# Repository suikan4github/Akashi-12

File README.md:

# Akashi-12
Study PCB for RP2040

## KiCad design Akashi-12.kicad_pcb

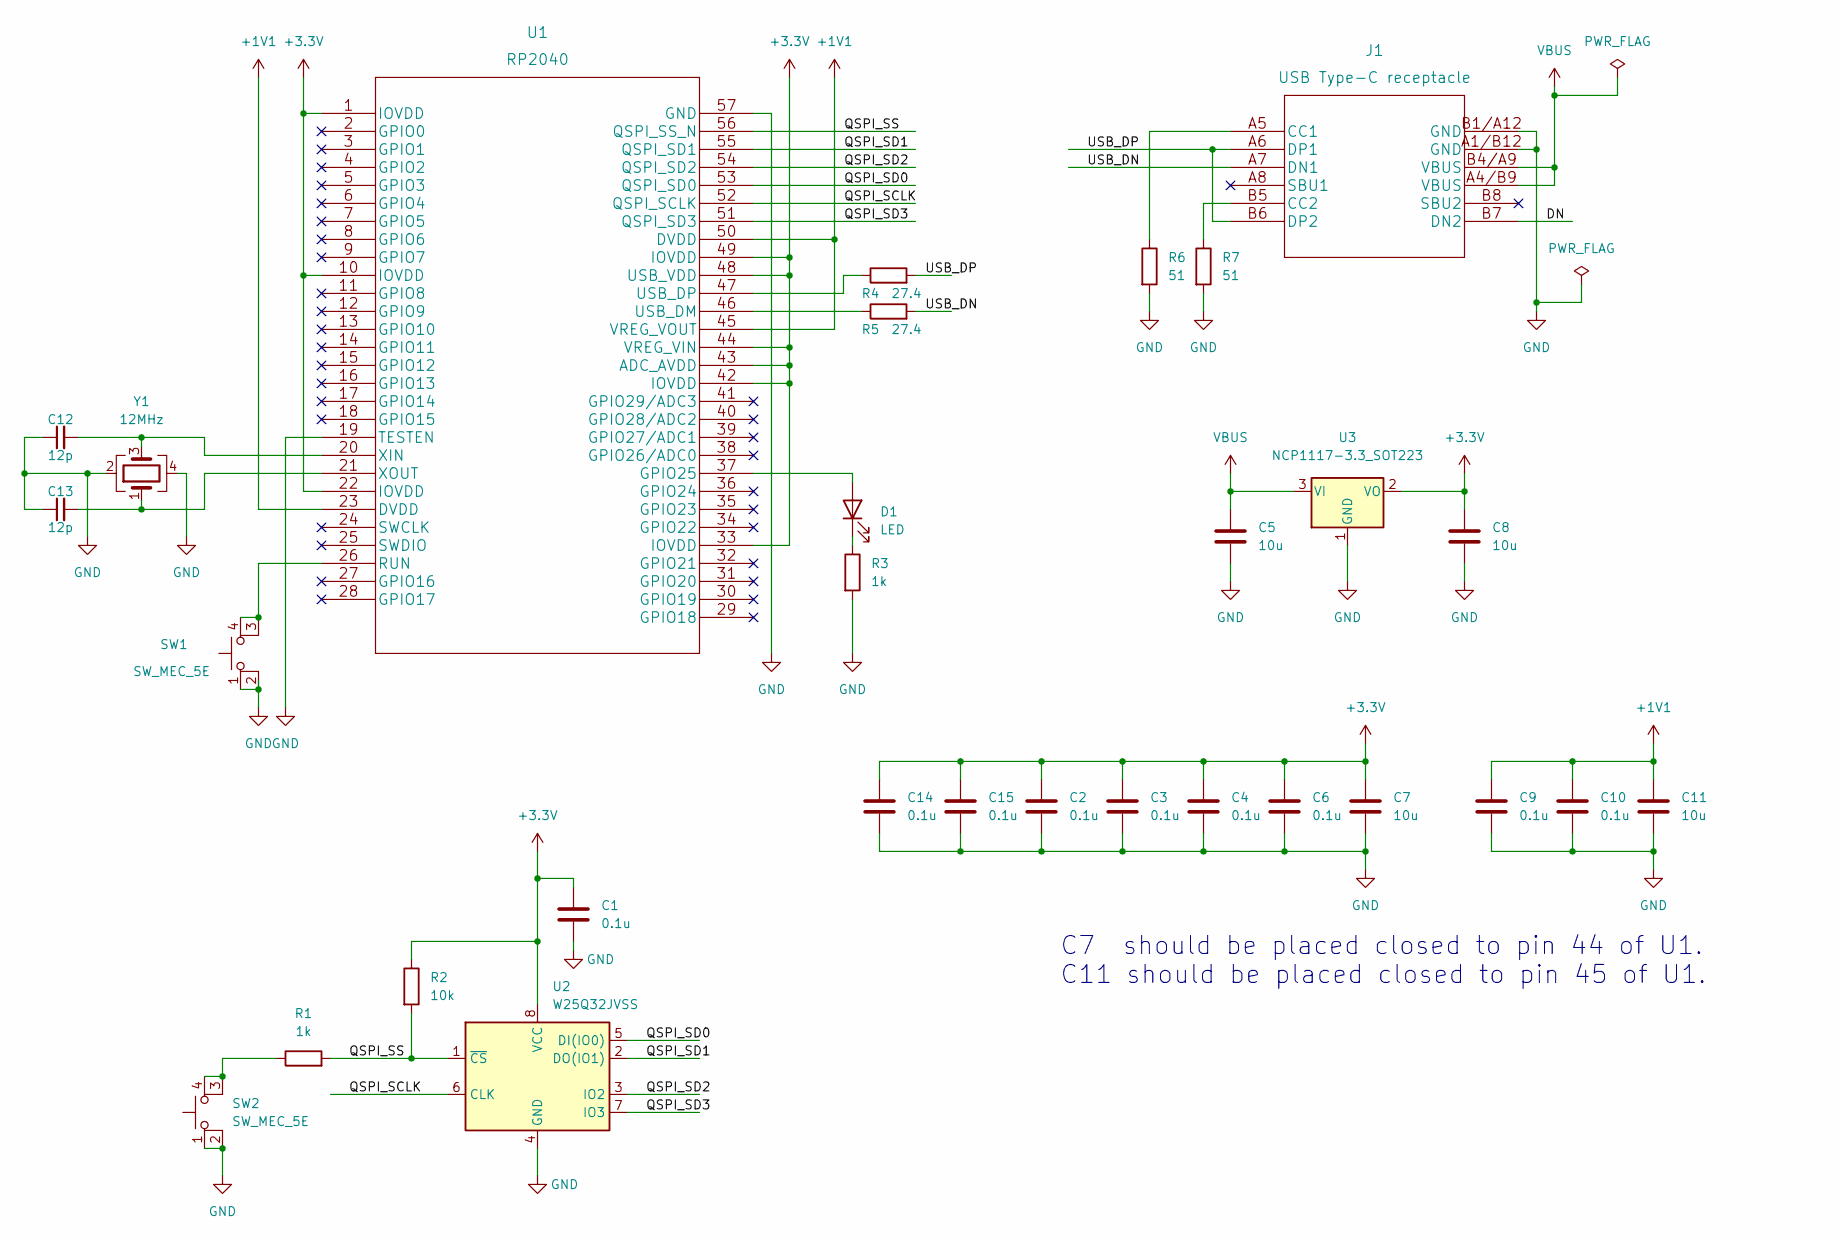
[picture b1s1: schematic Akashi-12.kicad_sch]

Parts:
C1, C2, C3, C4, C6, C9, C10, C14, C15: 0.1u; C_0603_1608Metric_Pad1.08x0.95mm_HandSolder
C5, C7, C8, C11: 10u; C_0603_1608Metric_Pad1.08x0.95mm_HandSolder; parts number GRM188R61C106MA73D
C12, C13: 12p; C_0603_1608Metric_Pad1.08x0.95mm_HandSolder
D1: LED; LED_D3.0mm
J1: USB Type-C receptacle; 2171790001; parts number 2171790001
R1, R3: 1k; R_0603_1608Metric_Pad0.98x0.95mm_HandSolder
R2: 10k; R_0603_1608Metric_Pad0.98x0.95mm_HandSolder
R4, R5: 27.4; R_0603_1608Metric_Pad0.98x0.95mm_HandSolder
R6, R7: 51; R_0603_1608Metric_Pad0.98x0.95mm_HandSolder
SW1, SW2: SW_MEC_5E; SW_TH_Tactile_Omron_B3F-10xx
U1: RP2040
U2: W25Q32JVSS; SOIC-8_5.23x5.23mm_P1.27mm; parts number W25Q32JVSS
U3: NCP1117-3.3_SOT223; SOT-223-3_TabPin2; parts number NCP1117-3.3_SOT223
Y1: 12MHz; Crystal_SMD_3225-4Pin_3.2x2.5mm_HandSoldering; parts number LFXTAL083388RL3K

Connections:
+1V1: C9.1, C10.1, C11.1, U1.23 (DVDD), U1.45 (VREG_VOUT), U1.50 (DVDD)
+3V3: C1.1, C2.1, C3.1, C4.1, C6.1, C7.1, C8.1, C14.1, C15.1, R2.1, U1.1 (IOVDD), U1.10 (IOVDD), U1.22 (IOVDD), U1.33 (IOVDD), U1.42 (IOVDD), U1.43 (ADC_AVDD), U1.44 (VREG_VIN), U1.48 (USB_VDD), U1.49 (IOVDD), U2.8 (VCC), U3.2 (VO)
/DN: J1.B7 (DN2)
/QSPI_SCLK: U1.52 (QSPI_SCLK), U2.6 (CLK)
/QSPI_SD0: U1.53 (QSPI_SD0), U2.5 (DI(IO0))
/QSPI_SD1: U1.55 (QSPI_SD1), U2.2 (DO(IO1))
/QSPI_SD2: U1.54 (QSPI_SD2), U2.3 (IO2)
/QSPI_SD3: U1.51 (QSPI_SD3), U2.7 (IO3)
/QSPI_SS: R1.2, R2.2, U1.56 (QSPI_SS_N), U2.1 (~CS)
/USB_DN: J1.A7 (DN1), R5.2
/USB_DP: J1.A6 (DP1), J1.B6 (DP2), R4.2
GND: C1.2, C2.2, C3.2, C4.2, C5.2, C6.2, C7.2, C8.2, C9.2, C10.2, C11.2, C12.1, C13.1, C14.2, C15.2, J1.A1/B12 (GND), J1.B1/A12 (GND), R3.2, R6.2, R7.2, SW1.1, SW1.2, SW2.1, SW2.2, U1.19 (TESTEN), U1.57 (GND), U2.4 (GND), U3.1 (GND), Y1.2, Y1.4
unnamed: C12.2, U1.20 (XIN), Y1.3
unnamed: C13.2, U1.21 (XOUT), Y1.1
unnamed: D1.1 (K), R3.1
unnamed: D1.2 (A), U1.37 (GPIO25)
unnamed: J1.A5 (CC1), R6.1
unnamed: J1.B5 (CC2), R7.1
unnamed: R1.1, SW2.3 (K), SW2.4 (A)
unnamed: R4.1, U1.47 (USB_DP)
unnamed: R5.1, U1.46 (USB_DM)
unnamed: SW1.3 (K), SW1.4 (A), U1.26 (RUN)
VBUS: C5.1, J1.A4/B9 (VBUS), J1.B4/A9 (VBUS), U3.3 (VI)

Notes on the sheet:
C7 should be placed closed to pin 44 of U1. C11 should be placed closed to pin 45 of U1.

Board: 2 copper layers, 30 parts (5 on the bottom side), 22 nets, no tracks yet.

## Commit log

2022-12-04 Schematics completes
2022-12-04 Place parts on the layout.
2022-12-10 Update layout and USB connector footpring

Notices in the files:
parts and their libraries:
Copyright 2021 Accelerated Designs. All rights reserved.
